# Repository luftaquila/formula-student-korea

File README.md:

# Formula Student Korea

- [Agent instructions](AGENTS.md): working constraints and required references
- [Development](CONTRIBUTING.md): commands, tests, logging, k3s deployment, and backup/restore
- [Architecture](docs/architecture.md): runtime boundaries and data ownership
- [API reference](docs/api.md): public and supporting-service contracts
- [Rover](rover/README.md): navigation, MCU, provisioning, and recovery
- [GPS](rover/gps/README.md): receiver runtime, base station, and provisioning
- [Timing hardware](competition/modules/traffic/DESIGN.md): wiring, wireless protocol, firmware, and verification

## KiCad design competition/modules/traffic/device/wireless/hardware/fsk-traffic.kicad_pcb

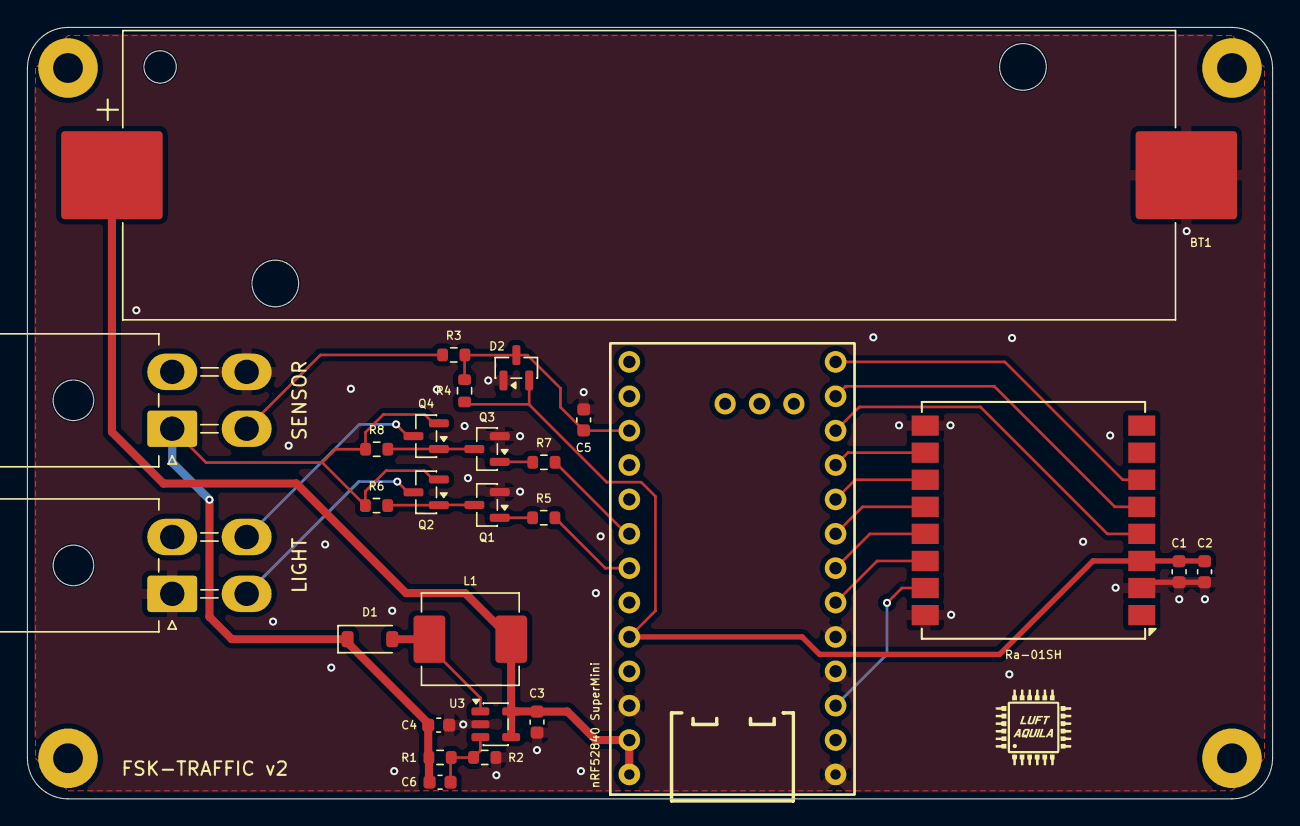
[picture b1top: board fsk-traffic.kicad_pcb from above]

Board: 2 copper layers, 92.0 x 57.0 mm, 27 parts (0 on the bottom side), 25 nets.

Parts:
BT1: 18650; BatteryHolder_Keystone_1042_1x18650
C1: 100nF; C_0603_1608Metric
C2, C3, C4: 10uF; C_0603_1608Metric
C5: 100pF; C_0603_1608Metric
C6: 47pF; C_0603_1608Metric
D1: B5819W; D_SOD-123
D2: BAT54S; SOT-23
J1: SENSOR; Molex_Mini-Fit_Jr_5569-04A2_2x02_P4.20mm_Horizontal
J2: LIGHT; Molex_Mini-Fit_Jr_5569-04A2_2x02_P4.20mm_Horizontal
L1: 22uH; L_Sunlord_MWSA0603S
Q1, Q3: MMBT3904; SOT-23
Q2, Q4: MMBT3906; SOT-23
R1: 1M; R_0603_1608Metric
R2: 110k; R_0603_1608Metric
R3: 330; R_0603_1608Metric
R4: 4.7k; R_0603_1608Metric
R5, R6, R7, R8: 10k; R_0603_1608Metric
U1: nRF52840 SuperMini; SuperMini_NRF52840
U2: Ra-01SH; Ai-Thinker-Ra-01-LoRa
U3: TPS61040DBV; SOT-23-5

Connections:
+3.3V: C1.1, C2.1, D2.2 (K), R4.2, U1.16 (3V3), U2.3 (VDD)
+12V: C4.1, C6.1, D1.1 (K), J1.1, Q2.2 (E), Q4.2 (E), R1.1, R6.1, R8.1
+BATT: BT1.1 (+), C3.1, L1.1, U1.13 (BAT+), U1.29 (BAT+), U3.4 (EN), U3.5 (VIN)
/BUSY: U1.9 (P1.00), U2.10 (DIO4)
/DIO1: U1.12 (P1.06-LF), U2.6 (DIO1)
/GN: J2.4, Q4.3 (C)
/GREEN: R7.2, U1.19 (P0.02-LF)
/MISO: U1.6 (P0.20), U2.13 (MISO)
/MOSI: U1.5 (P0.17), U2.14 (MOSI)
/NRST: U1.10 (P0.11), U2.4 (~RESET)
/NSS: U1.2 (P0.08), U2.15 (~NSS)
/RD: J2.3, Q2.3 (C)
/RED: R5.2, U1.18 (P0.29-LF)
/RXEN: U1.8 (P0.24), U2.11 (DIO5)
/SCK: U1.7 (P0.22), U2.12 (SCK)
/SENSE: J1.3, R3.1
/SENSOR: C5.1, D2.3 (COM), R3.2, R4.1, U1.22 (P1.11-LF)
/TXEN: U1.11 (P1.04-LF), U2.5 (DIO0)
GND: BT1.2 (-), C1.2, C2.2, C3.2, C4.2, C5.2, D2.1 (A), J1.4, J2.1, Q1.2 (E), Q3.2 (E), R2.2, U1.3 (GND), U1.4 (GND), U1.14 (GND), U1.28 (GND), U2.2 (GND), U2.9 (GND), U2.16 (GND), U3.2 (GND)
unnamed: D1.2 (A), L1.2, U3.1 (SW)
unnamed: Q1.1 (B), R5.1
unnamed: Q1.3 (C), Q2.1 (B), R6.2
unnamed: Q3.1 (B), R7.1
unnamed: Q3.3 (C), Q4.1 (B), R8.2
unnamed: C6.2, R1.2, R2.1, U3.3 (FB)

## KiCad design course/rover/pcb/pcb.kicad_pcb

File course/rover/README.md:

# FSK Rover

Raspberry Pi 5 + RTK GPS rover. Drives a waypoint mission, sprays a
marker at each cone. Podman container on AlmaLinux bootc; Tailscale
for remote access.

## Hardware

| Role | Part | Interface |
|------|------|-----------|
| Compute | Raspberry Pi 5 | — |
| Coprocessor | Waveshare RP2040-Zero | USB CDC (`/dev/ttyMCU`) |
| GPS | u-blox ZED-F9P | USB CDC (`/dev/ttyGPS`) |
| RTK corrections | NTRIP caster (NGII) | TCP |
| Motor driver | Cytron MDD10A | MCU PWM + DIR |
| Drive | 2× MD36L P27 DC gearmotor (27:1) on Wheeltec R550 rear | one MDD10A channel per wheel |
| Wheel encoders | 2× quadrature on motor shaft, 3.3 V push-pull, 500 PPR (×4 × 27 = 54000 counts/wheel rev); XH2.54-4P connector | MCU PIO + 3V3 |
| Wheels | 125 mm dia (Wheeltec R550) | rear drive, front passive |
| Steering servo | Wheeltec S20F (5–6.5 V, 20 kg·cm, stall 1.8 A) | MCU PWM |
| Spray/dispenser servo | MG995 | MCU PWM (GP6) |
| E-Stop | NC momentary, fail-safe | MCU GP7, internal pull-up |
| Status sticks | 2× NeoPixel Stick (8× WS2812 each) | MCU PIO via 2N7002 level shifter (GP11); mirrors onboard LED 1:1 |
| Nav lights | red/green, 3-pin module (+5V/GND/control) | MCU GP9 direct on/off; steady on |
| Platform | Wheeltec R550 AKM Plus | Ackermann |
| Battery | 25.6 V (8S) LiFePO4, 6.6 Ah | XT60, BMS |
| Pi supply | 5 V 5 A buck → USB-C PD | Pi only |
| Servo supply | MP1584EN @ 5.5 V, ≥3 A | S20F + dispenser + NeoPixel sticks + nav lights |

The Pi drives no GPIO: the dispenser/spray servo PWM moved to the MCU
(GP6 — see Pinout below). `spray_node` only computes the pulse width and
forwards it via `mcu_bridge_node` as `D <us>`.

### Power chain

```
25.6 V LiFePO4 8S 6.6 Ah ─┬─► 5 V 5 A buck ──────► Pi 5 (USB-C PD)
                         ├─► MDD10A V_MOT ─────► rear DC motors
                         └─► MP1584EN @ 5.5 V ─► S20F + spray VCC
```

- All GNDs commoned.
- Battery thresholds: warn 22 V, undervolt cutoff 20 V.
- MP1584EN abs. max 30 V; 8S full charge 29.2 V is in range. LM2596HV (60 V) for margin.

### Drive control split

- **MCU**: encoders, motor PWM, steering, dispenser servo, battery ADC,
  E-Stop, status LEDs (onboard + external sticks), nav lights, WDTs.
  Pi link USB CDC @ 50 Hz.
- **Pi**: navigation, RTK, course bridge, dispense sequencing (servo PWM
  on the MCU).

Bridge: `mcu_bridge_node`. Firmware CI: `.github/workflows/rover-mcu.yml`.

## Architecture

Five ROS 2 Jazzy nodes in the rootful `pilot` container, `--network=host` (a
separate `perception` container handles camera streaming + stereo obstacle
detection — it joins this same ROS graph and publishes `/rover/perception/obstacle`,
which `navigator_node` turns into a local mission pause; see `perception/`):

```
course server (port 10000)
        │
        │  SSE /api/rover/stream    ← execute-path, request-position,
        │                              emergency-stop, manual-control
        │  POST /api/rover/position      ┐
        │       /api/rover/telemetry     │  (from the rover)
        │       /api/rover/status        ┘
        │
    bridge_node
        │
 ┌──────┴──────────────── topics ───────────────────────┐
 │                                                      │
 gps_node ── /rover/gps/{position,heading,fix_status} ─┐
 gps_node ── /rover/ntrip/status ──────────────────────┤
                                                       ▼
                                               navigator_node
                                                 │        │
                      /rover/cmd/velocity ◄──────┘        │
                          ▼                               │
                  mcu_bridge_node ── USB CDC ── RP2040    │
                                                /rover/nav/waypoint_reached
                                                          │
                                                   spray_node ── /rover/spray/done
```

Hot-plug behaviour:

- `pilot-run` probes `/dev` at start and passes only present devices to `podman run --device`.
- udev `add|remove` on GPS/MCU fires `fsk-pilot-replug.service`, which debounces and restarts `pilot.service`.
- Container restart latency: ~5 s.
- A missing device doesn't block the others.

### Mission state machine (`navigator_node`)

```
IDLE → CALIBRATING → NAVIGATING → SETTLING → SPRAYING ─(next wp)→ NAVIGATING
                                                           │
                              (all wp done, return_to_start)│
                                                           ▼
                                              NAVIGATING (return) → IDLE

IDLE → CAL_ANTENNA → IDLE   (operator-triggered antenna-offset auto-cal)
IDLE → CAL_WHEELS  → IDLE   (operator-triggered per-wheel scale auto-cal)

any state → EMERGENCY_STOP (on /rover/cmd/emergency_stop)
any driving state → ERROR  (GPS timeout / fix below quality > fix_hysteresis_s,
                            or battery below battery_abort_pct mid-mission)
```

- **Antenna-precise docking**: every waypoint becomes a *cruise* segment
  followed by a *dock* segment — a straight corridor of length
  `dock_approach_distance` ending at the chassis pose where the GPS
  antenna sits exactly on the user's clicked target. The chassis dock
  pose is `target − R(ψ_dock) · antenna_offset`, so non-zero antenna
  offset is compensated at planning time. The dock corridor is straight
  so ω ≈ 0 at arrival, which makes antenna position predictable from
  chassis pose alone. `dock_approach_distance` is clamped per-segment
  to ≤ ½ · inter-waypoint span (floor 0.3 m), so tightly-spaced cones
  don't get an entry point projected behind the previous waypoint.
- **State estimator** fuses MCU encoder odometry (chassis v, ω) with GPS
  antenna position and GPS heading-of-motion (with antenna-offset
  inversion) into a chassis (x, y, ψ) at 20 Hz. ψ never depends on raw
  GPS heading-of-motion alone — that decouples control from the 200–500
  ms heading-of-motion latency that previously caused figure-8 swings.
- **CALIBRATING**: drive κ = 0 at `calibration_speed`, regress chassis
  heading from antenna ENU samples. Trustworthy when chord ≥
  `calibration_chord_min_m` AND residual RMS ≤ `calibration_residual_max`
  (production: 1.5 m / 5 cm → ~2° heading 1σ), otherwise extend once
  and ERROR if still bad. Hard cap at `calibration_max_distance`.
- **NAVIGATING/cruise**: Pure Pursuit with D-term damping +
  virtual-lookahead projection past the goal. `max_curvature` 1.2 1/m
  matches `tan(25°)/wheelbase`; speed scales with `cos(α)` and tapers
  linearly from `cruise_speed` toward `approach_speed` over the last
  `pp_handoff_blend_distance` metres so the chassis enters the dock
  corridor at the speed DockTracker's gains were tuned for.
- **NAVIGATING/dock**: state-feedback line follower on antenna lateral
  error: κ = −k_y · e_y_antenna − k_ψ · e_ψ − k_i · ∫e_y dt. The
  integral term (with anti-windup at `dock_integral_limit`) cancels
  steady κ-bias from antenna-offset residual / mast tilt / slope.
  Reverses straight on along-track overshoot.
- **SETTLING → SPRAYING**: antenna within `settle_tolerance` for
  `settle_readings` consecutive samples → fire. Drift back outside
  `waypoint_tolerance` mid-settle hands control back to the dock tracker.
- **CAL_ANTENNA**: drive a chord then a sinusoidal-κ S-curve and run
  closed-form LSQ on the (chassis pose, antenna obs) samples. The
  solver gates on a minimum ψ excitation (`SOLVE_PSI_SPREAD_MIN_RAD`)
  so a SCURVE that didn't actually rotate the rover (encoder stall,
  mid-drive E-Stop) can't silently persist a garbage offset. Result
  written to `$PILOT_STATE_DIR/antenna_offset.json`.
- **CAL_WHEELS**: drive a straight 10 m chord at `wheel_cal_speed` and
  divide GPS chord distance by per-wheel encoder integration to recover
  per-wheel rolling-radius scale. Result written to
  `$PILOT_STATE_DIR/wheel_cal.json` and applied live via
  `/rover/cmd/apply_wheel_scales`. Bounded to ±15 % so encoder
  slip / GPS error never produces a runaway scale.

Thresholds in `pilot/config/rover_params.yaml`. The most physically
load-bearing knob is `antenna_offset_x` / `antenna_offset_y` — measure
it once on the actual chassis with a tape (or run CAL_ANTENNA once);
everything else self-corrects via GPS feedback.

Fleet-wide identical: hardware, NTRIP endpoint, `rover_params.yaml`. Per-rover differs only in `SERVER_URL` / `INTERNAL_SECRET` / `NTRIP_USERNAME`.

## Image structure

| Image | Built by | Updates | Owns |
|-------|----------|---------|------|
| `ghcr.io/luftaquila/fsk-rover-host:{candidate,edge,vX.Y.Z}` | `host/Containerfile` | `bootc upgrade` (24 h, reboot) | AlmaLinux 10 + Pi 5 firmware/DTB, NM, sshd, tailscale, podman, udev, `pilot.service` + `pilot-run`, `perception.service` + `perception-run`, fsk user |
| `ghcr.io/luftaquila/fsk-rover-pilot:{candidate,edge,vX.Y.Z}` | `pilot/Containerfile` | `podman auto-update` (24 h, in-place) | ROS 2 Jazzy + the five `pilot` nodes |
| `ghcr.io/luftaquila/fsk-rover-perception:{candidate,edge,vX.Y.Z}` | `perception/Containerfile` | `podman auto-update` (24 h, in-place) | OpenCV camera streamer + stereo obstacle detection (see `perception/`) |

- Host base: `quay.io/almalinuxorg/almalinux-bootc-rpi:10`.
- Stock `almalinux-bootc:10` lacks Pi 5 firmware and won't boot.

## Provisioning

1. **Build SD image** — manual dispatch `rover-sd-image.yml`. Auto-resolves
   the latest AlmaLinux gpt-10-arm64, applies fan dtparams, bakes a
   one-shot `fsk-firstboot.service` (`bootc switch …:candidate &&
   reboot`). Artifact: `fsk-rover-sd.img.xz`.

2. **Flash + boot**. Pi reboots once mid-bring-up. After ~60 s: IP on
   `eth0` (DHCP) or `wlan0` (default `fsk-default`: SSID `default`,
   PSK `password`). `pilot.service` restart-loops until step 3.

3. **Provision** (admin workstation, SSH key in <https://github.com/luftaquila.keys>):
   ```bash
   scripts/provision-rover.sh <rover-ip> [--ntrip-username=<id>]
   ```
   Reads `INTERNAL_SECRET`, `PUBLIC_URL` from `.env`. Idempotent.

4. **Wi-Fi**:
   ```bash
   ssh fsk@<rover-ip> sudo nmcli connection modify fsk-default \
       802-11-wireless.ssid 'MyAP' wifi-sec.psk 'mypassword'
   ssh fsk@<rover-ip> sudo nmcli connection up fsk-default
   ```

5. **Tailscale** (off-LAN):
   ```bash
   ssh fsk@<rover-ip> sudo tailscale up --auth-key=tskey-…
   ```

6. **Verify**:
   ```bash
   ssh fsk@<rover-ip> systemctl status pilot.service
   ssh fsk@<rover-ip> sudo journalctl -u pilot.service -n 50
   ```

7. **Pre-competition freeze**:
   ```bash
   ssh fsk@<rover-ip> sudo systemctl disable --now \
       bootc-fetch-apply-updates.timer podman-auto-update.timer
   ```

### Recovery

Unreachable (no LAN, no Tailscale) → reflash SD. On-rover: `bootc rollback`.

## Runtime configuration

| Knob | Storage | Change with |
|------|---------|-------------|
| `INTERNAL_SECRET` | podman secret `internal-secret` | `printf '%s' $val \| sudo podman secret create internal-secret -` |
| `NTRIP_USERNAME` | podman secret `ntrip-username` | same pattern |
| `SERVER_URL`, `ROS_DOMAIN_ID` | `/etc/pilot/pilot.conf` | `sudo $EDITOR /etc/pilot/pilot.conf` |
| Wi-Fi | `/etc/NetworkManager/system-connections/fsk-default.nmconnection` | `sudo nmcli connection modify fsk-default …` |
| Mission params | `pilot/config/rover_params.yaml` (baked) | new pilot build → push → auto-update |
| OTA channel | `bootc status` (host); `pilot-run` `IMAGE=` (pilot) | `sudo bootc switch …:edge`; rebake host |
| OTA freeze | both timers | `sudo systemctl disable --now <timer>` |

After changing `pilot.conf` or any secret: `sudo systemctl restart pilot.service`.

Fixed NTRIP settings (NGII):

| Field | Value |
|-------|-------|
| host:port | `www.gnssdata.or.kr:2101` |
| password | `gnss` |
| mountpoint | auto-selected (nearest base, RTCM 3.2) |

Battery calibration:

- File: `/var/lib/pilot/battery_cal.json` (host bind-mount).
- Persists across `systemctl restart`, `podman auto-update`, `bootc upgrade`.
- Bounds: `measured_v ∈ [15, 32] V`, `gain ∈ [0.5, 2.0]`. OOB → reset to `gain = 1.0`.

Antenna offset calibration (CAL_ANTENNA):

- File: `/var/lib/pilot/antenna_offset.json` (host bind-mount).
- Persisted `(a_x, a_y)` overrides the YAML default; absent / corrupt → fall back to YAML.
- Bounds: `|a_x|, |a_y| ≤ 1 m`, RMS residual ≤ 5 cm, ψ excitation ≥ 8.6° (rejects SCURVEs that didn't actually rotate the rover).

Wheel scale calibration (CAL_WHEELS):

- File: `/var/lib/pilot/wheel_cal.json` (host bind-mount).
- Persisted `(scale_l, scale_r)` is applied live by `mcu_bridge_node` as `v_wheel_corrected = v_wheel_raw × scale`.
- Bounds: `scale ∈ [0.85, 1.15]`, GPS chord ≥ 5 m, ≥ 50 samples (1 s @ 50 Hz). OOB → reject and refuse to persist (caller falls back to current live scale).

## OTA & rollback

```bash
# Host (rare; reboot to apply)
sudo bootc status
sudo systemctl start bootc-fetch-apply-updates.service
sudo bootc rollback && sudo systemctl reboot

# Pilot (frequent; in-place)
sudo systemctl start podman-auto-update.service
sudo podman pull ghcr.io/luftaquila.../fsk-rover-pilot:edge \
  && sudo systemctl restart pilot.service
```

State:

```bash
sudo bootc status
systemctl status pilot.service
sudo podman ps
sudo podman secret ls
sudo journalctl -u pilot.service -n 200
```

## MCU coprocessor (`mcu/`)

### Pinout

| Role | Pin | Notes |
|------|-----|-------|
| Left enc B/A | GP2, GP3 | PIO consecutive pins; lower = bit 0 |
| Right enc B/A | GP4, GP5 | |
| E-Stop | GP7 | NC + pull-up; HIGH = tripped |
| Steering servo | GP8 | S20F signal |
| Dispenser servo | GP6 | MG995 signal; slice3 chA |
| Left mot PWM/DIR | GP15, GP27 | → MDD10A (PWM slice7B; DIR digital) |
| Right mot PWM/DIR | GP28, GP29 | → MDD10A (PWM slice6A; DIR digital) |
| Onboard status LED | GP16 | onboard WS2812 |
| Ext NeoPixel data | GP11 | 16-LED stick chain via 2N7002 shifter (firmware-inverted) |
| Nav lights | GP9 | red/green 3-pin module (+5V/GND/control), direct on/off |
| Battery V | GP26 (ADC0) | 100 kΩ : 10 kΩ |

### Firmware internals

- PIO0 SM0/SM1: quadrature decoders.
- PIO1 SM0: onboard WS2812. PIO1 SM1: external 16-LED stick chain (mirrors onboard 1:1).
- GP11 (ext LEDs) inverted via `gpio_set_outover` to cancel the 2N7002 level shifter; idle line stays low so the WS2812 reset gap is preserved.
- Nav lights (GP9): held on at boot, steady; on/off only (no PWM).
- Encoder VCC/signal off RP2040 3V3 rail.
- E-Stop fail-safe: open contact → tripped.

### Battery divider

```
Vbat ─[100 kΩ 1%]─┬─ GP26 (ADC0)
                  ├─ 100 nF ─ GND
                  └─[10 kΩ 1%]─ GND
```

### SOC mapping (8S LiFePO4)

- `mcu_bridge_node` does piecewise-linear OCV-SOC interpolation (LiFePO4 is flat 20–90 % SOC, so linear maps fail).
- Above 27.20 V → 100 %; below 20.00 V → 0 %.
- `voltage` = calibrated; `voltage_raw` = uncorrected ADC.

### Field calibration (1-point gain)

Operator path: battery popover → "전압 보정" → enter multimeter reading.

Pipeline:

```
POST /api/rover/calibrate-battery
  → SSE → bridge_node → /rover/cmd/calibrate_battery
  → gain = measured_v / V_raw
  → $PILOT_STATE_DIR/battery_cal.json
```

### USB CDC protocol

Line-based ASCII, `\n` terminated.

Pi → MCU:

| Cmd | Args | Meaning |
|-----|------|---------|
| `H` | — | Heartbeat |
| `M` | `<l_duty> <r_duty> <steer_us>` | Raw duty [-1,1]; sets RAW lane |
| `V` | `<l_mps> <r_mps> <steer_us>` | Closed-loop; sets PID lane |
| `E` | — | SW E-Stop |
| `C` | — | Clear SW E-Stop latch (a still-open HW line stays tripped) |
| `P` | `<kp> <ki> <kd>` | PID gains |
| `L` | `<0\|1>` | PID gate (`1` allow, `0` force RAW) |
| `K` | `<pulse_duty> <pulse_ms> <fire_above_mps>` | Brake-pulse params |
| `A` | — | Arm one brake pulse on the next setpoint-deadband entry |
| `D` | `<pulse_us>` | Dispenser servo target (independent of M/V) |
| `N` | `<0\|1>` | Nav fault from Pi (GPS lost): `1` set, `0` clear |
| `B` | — | Reboot to BOOTSEL; emits `! BOOTSEL` first |

PID runs only when `L 1` AND last setpoint was `V`.

MCU → Pi @ 50 Hz: `T <ms> <enc_l> <enc_r> <vel_l> <vel_r> <vbat> <flags>`

Flags (hex):

| Bit | Meaning |
|-----|---------|
| 0 | E-Stop |
| 1 | Pi heartbeat timeout |
| 2 | Battery undervolt (≤ 20 V — motors gated) |
| 3 | Battery warn (≤ 22 V) |
| 4 | PID active |
| 5 | Last boot from HW WDT |
| 6 | Nav GPS lost (Pi-reported; chassis stopped Pi-side) |
| 7 | Raw E-Stop line (physical button/wire HIGH; bit 0 also ORs the SW latch) |

Async: `! <msg>` (e.g. `! WDT TIMEOUT`).

### Status LED

| Color | State |
|-------|-------|
| dim white | boot |
| green | idle |
| blue | driving |
| yellow | heartbeat timeout / battery warn |
| magenta | undervolt |
| orange blink | nav GPS lost |
| red blink | E-Stop |

The two external NeoPixel Sticks (16 LEDs, GP11) mirror this onboard LED 1:1
— same colour and blink. The nav lights (GP9) are independent: steady on
whenever the MCU is powered, not tied to status.

### Build

```bash
sudo apt install cmake gcc-arm-none-eabi libnewlib-arm-none-eabi \
                 libstdc++-arm-none-eabi-newlib build-essential
git clone --depth 1 --recurse-submodules \
    https://github.com/raspberrypi/pico-sdk.git ~/pico-sdk
export PICO_SDK_PATH=~/pico-sdk
cmake -S course/rover/mcu -B course/rover/mcu/build -DPICO_BOARD=pico
cmake --build course/rover/mcu/build -j
```

Output: `build/rover_mcu.uf2`. Overrides (defaults r=62.5 mm, PPR=500, gear=27):
`-DWHEEL_RADIUS_M=… -DENCODER_PPR=… -DGEAR_RATIO=…`.

### Flash

| Context | Command |
|---------|---------|
| First time | hold BOOT, plug USB-C, drag `.uf2` to `RPI-RP2` |
| Rover Pi | `sudo flash-mcu rover_mcu.uf2` (pauses pilot for the duration) |
| Off-rover | `picotool load -f rover_mcu.uf2 && picotool reboot` |

Address as `/dev/ttyMCU` — `/dev/ttyACM*` ordering is non-deterministic.

> Current sensing intentionally omitted: MDD10A self-protects, encoder-vel = 0 with non-zero command covers stall. Re-add `current.c` + `FLAG_OVERCURRENT` if a shunt-amp lands.

## CI

| Workflow | Trigger | Output |
|----------|---------|--------|
| `rover-pilot-image.yml` | `main` push under `pilot/**`; manual | `fsk-rover-pilot` OCI; pytest gate |
| `rover-perception-image.yml` | `main` push under `perception/**`; manual | `fsk-rover-perception` OCI; compileall + pytest gate |
| `rover-host-image.yml` | `main` push under `host/**`; manual | `fsk-rover-host` OCI |
| `rover-sd-image.yml` | manual only | `fsk-rover-sd.img.xz` |
| `rover-mcu.yml` | `main` push under `mcu/**`; manual | `rover_mcu.uf2` |

## Release channels

| Trigger | Channel | Rollout |
|---------|---------|---------|
| `main` push | `:candidate` | auto-pull within 24 h |
| dispatch `edge` | `:edge` | `sudo bootc switch …:edge`; rebake host for pilot |
| dispatch `vX.Y.Z` | `:vX.Y.Z` | rollback reference |

- Default channel: `:candidate`.
- Re-disable both timers after manual upgrades.

## Local development (no rover)

```bash
mkdir -p ~/pilot_ws/src
ln -s "$(pwd)/pilot" ~/pilot_ws/src/pilot
cd ~/pilot_ws
source /opt/ros/jazzy/setup.bash
pip install -r src/pilot/requirements.txt
colcon build --packages-select pilot
source install/setup.bash

INTERNAL_SECRET=… NTRIP_USERNAME=YOUR_NGII_LOGIN PILOT_STATE_DIR=/tmp \
  ros2 launch pilot pilot.launch.py \
    server_url:=https://your-server.example/course
```

<details>
<summary>Mirror the rover's <code>/dev/tty{GPS,MCU}</code> symlinks (only if your dev box has these devices)</summary>

```bash
sudo install -m 644 \
    "$(pwd)/host/files/usr/lib/udev/rules.d/99-fsk-rover.rules" \
    /etc/udev/rules.d/99-fsk-rover.rules
sudo udevadm control --reload-rules
sudo udevadm trigger --subsystem-match=tty
```
</details>

Single-node:

```bash
ros2 run pilot gps_node --ros-args --params-file src/pilot/config/rover_params.yaml
ros2 topic echo /rover/gps/position
```

## Tests

```bash
cd course/rover/pilot && python3 -m pytest test/ -q
npm run test:course
npm run test:shared
```

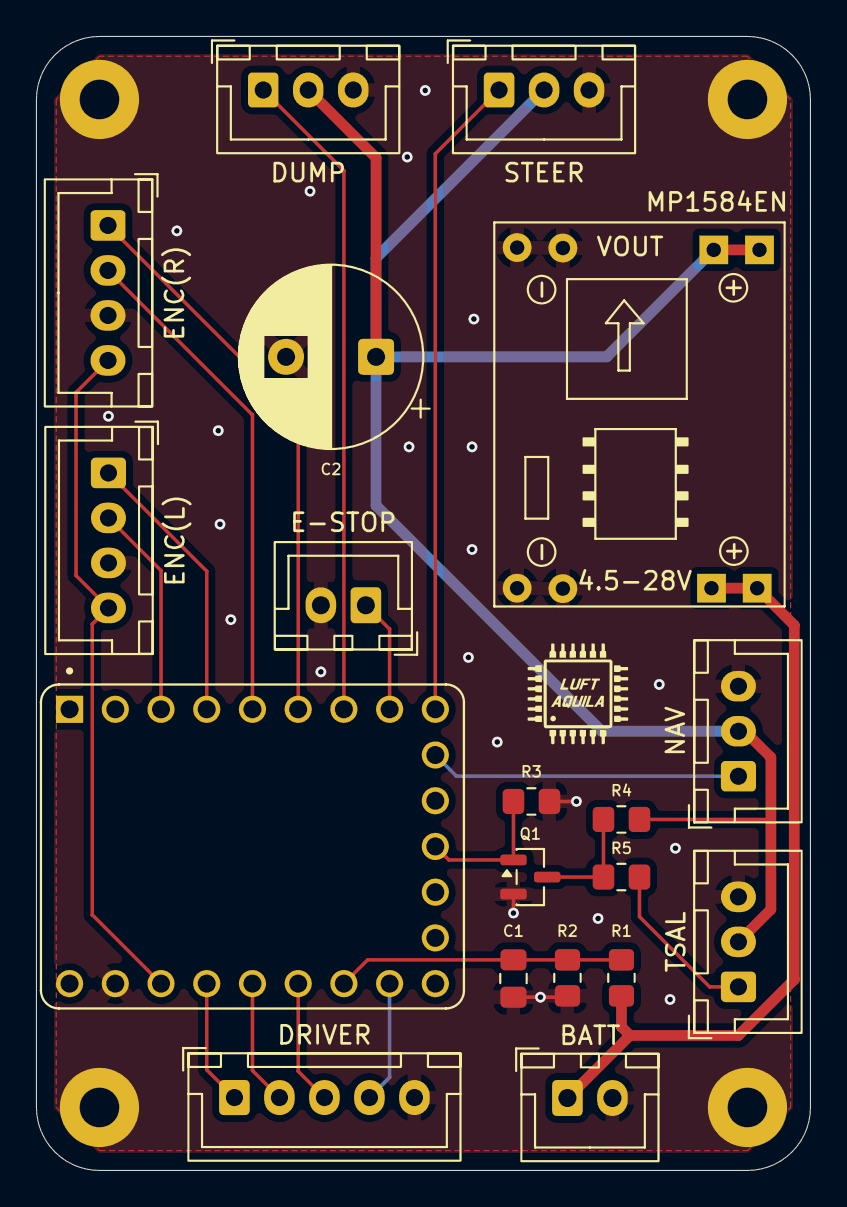
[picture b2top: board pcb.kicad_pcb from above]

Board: 2 copper layers, 43.0 x 63.0 mm, 23 parts (0 on the bottom side), 20 nets.

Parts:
C1: 100nF; C_0805_2012Metric_Pad1.18x1.45mm_HandSolder
C2: 3300uF; CP_Radial_D10.0mm_P5.00mm
H1, H2, H3, H4: MountingHole_Pad; MountingHole_2.2mm_M2_Pad
J1: BATT; JST_XH_B2B-XH-A_1x02_P2.50mm_Vertical
J2: E-STOP; JST_XH_B2B-XH-A_1x02_P2.50mm_Vertical
J3: NAV; JST_XH_B3B-XH-A_1x03_P2.50mm_Vertical
J4: STEER; JST_XH_B3B-XH-A_1x03_P2.50mm_Vertical
J5: DUMP; JST_XH_B3B-XH-A_1x03_P2.50mm_Vertical
J6: TSAL; JST_XH_B3B-XH-A_1x03_P2.50mm_Vertical
J7: ENC(L); JST_XH_B4B-XH-A_1x04_P2.50mm_Vertical
J8: ENC(R); JST_XH_B4B-XH-A_1x04_P2.50mm_Vertical
J9: DRIVER; JST_XH_B5B-XH-A_1x05_P2.50mm_Vertical
Q1: 2N7002; SOT-23
R1, R3: 100k; R_0805_2012Metric_Pad1.20x1.40mm_HandSolder
R2: 10k; R_0805_2012Metric_Pad1.20x1.40mm_HandSolder
R4: 470; R_0805_2012Metric_Pad1.20x1.40mm_HandSolder
R5: 330; R_0805_2012Metric_Pad1.20x1.40mm_HandSolder
U1: RP2040-ZERO; MODULE_RP2040-ZERO
U2: MP1584EN; SRT_MPT1584EN_Module

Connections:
+3.3V: J7.4, J8.4, U1.21 (3V3)
+5V: C2.1, J3.2, J4.2, J5.2, J6.2, R4.1, U2.3 (OUT+)
+BATT: J1.1, R1.1, U2.1 (IN+)
/DIR(L): J9.3, U1.18 (GP27)
/DIR(R): J9.1, U1.20 (GP29)
/DOUT: Q1.1 (G), R3.1, U1.12 (GP11)
/DUMP: J5.1, U1.7 (GP6)
/ENC(L)-A: J7.1, U1.4 (GP3)
/ENC(L)-B: J7.2, U1.3 (GP2)
/ENC(R)-A: J8.1, U1.6 (GP5)
/ENC(R)-B: J8.2, U1.5 (GP4)
/ESTOP: J2.1, U1.8 (GP7)
/NAV: J3.1, U1.10 (GP9)
/PWM(L): J9.4, U1.16 (GP15)
/PWM(R): J9.2, U1.19 (GP28)
/SENSE: C1.1, R1.2, R2.1, U1.17 (GP26)
/STEER: J4.1, U1.9 (GP8)
/TSAL: J6.1, R5.2
GND: C1.2, C2.2, H1.1 (1_1), H2.1 (1_1), H3.1 (1_1), H4.1 (1_1), J1.2, J2.2, J3.3, J4.3, J5.3, J6.3, J7.3, J8.3, J9.5, Q1.2 (S), R2.2, R3.2, U1.22 (GND), U2.2 (IN-), U2.4 (OUT-)
unnamed: Q1.3 (D), R4.2, R5.1

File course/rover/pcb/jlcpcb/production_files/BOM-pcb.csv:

Comment,Designator,Footprint,LCSC,Quantity
RP2040-ZERO,U1,MODULE_RP2040-ZERO,,1
BATT,J1,JST_XH_B2B-XH-A_1x02_P2.50mm_Vertical,,1
100k,R3,R_0805_2012Metric_Pad1.20x1.40mm_HandSolder,,1
ENC(L),J7,JST_XH_B4B-XH-A_1x04_P2.50mm_Vertical,,1
100nF,C1,C_0805_2012Metric_Pad1.18x1.45mm_HandSolder,,1
ENC(R),J8,JST_XH_B4B-XH-A_1x04_P2.50mm_Vertical,,1
10k,R2,R_0805_2012Metric_Pad1.20x1.40mm_HandSolder,,1
3300uF,C2,CP_Radial_D10.0mm_P5.00mm,,1
2N7002,Q1,SOT-23,,1
TSAL,J6,JST_XH_B3B-XH-A_1x03_P2.50mm_Vertical,,1
470,R4,R_0805_2012Metric_Pad1.20x1.40mm_HandSolder,,1
330,R5,R_0805_2012Metric_Pad1.20x1.40mm_HandSolder,,1
MP1584EN,U2,SRT_MPT1584EN_Module,,1
DUMP,J5,JST_XH_B3B-XH-A_1x03_P2.50mm_Vertical,,1
STEER,J4,JST_XH_B3B-XH-A_1x03_P2.50mm_Vertical,,1
DRIVER,J9,JST_XH_B5B-XH-A_1x05_P2.50mm_Vertical,,1
NAV,J3,JST_XH_B3B-XH-A_1x03_P2.50mm_Vertical,,1
E-STOP,J2,JST_XH_B2B-XH-A_1x02_P2.50mm_Vertical,,1
100k,R1,R_0805_2012Metric_Pad1.20x1.40mm_HandSolder,,1
